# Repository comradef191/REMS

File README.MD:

# The RepRap Expansion Module System
A simple, open-source expansion system allowing easy addition of SPI, I2C, and GPIO devices to a controllerboard.

See [STANDARD.MD](Standard/STANDARD.MD) for details on module and slot design.
The KiCad footprint and symbol can be found in the [`/Footprint-Symbol`](/Footprint-Symbol) directory.

# Modules:

| Creator | Name           | Comment / Description                                          | Path                                      | Last Changed    |
|---------|----------------|----------------------------------------------------------------|-------------------------------------------|-----------------|
| Pera    | TLA2518 Module | Single-Sided SMD; Uses a TLA2518 to add 8 ADC inputs, over SPI. Untested. | [`Modules/TLA2518-8xThermistor`](Modules/TLA2518-8xThermistor) | March 22nd, 2024|

# License
Unless otherwise indicated, the contents of the [`/Modules`](/Modules) directory are licensed under CERN-OHL-v2+, see [LICENSE.txt](LICENSE.txt) for more details.

The contents of the [`/Standard`](/Standard) directory are licensed under CC0, see [CC0.txt](CC0.txt) for more details.

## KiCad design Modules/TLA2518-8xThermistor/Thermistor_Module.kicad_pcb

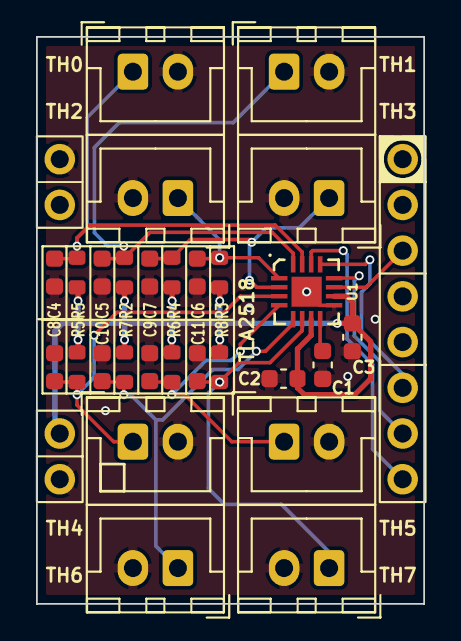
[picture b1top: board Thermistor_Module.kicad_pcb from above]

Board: 2 copper layers, 21.5 x 31.5 mm, 29 parts (0 on the bottom side), 15 nets.

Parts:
C1, C2, C3: 1uF; C_0603_1608Metric
C4, C5, C6, C7, C8, C9, C10, C11: 10uF; C_0603_1608Metric-DeSilked
J1, J2, J3, J4, J5, J6, J7, J8: Conn_01x02; JST_XH_B2B-XH-A_1x02_P2.50mm_Vertical
R1, R2, R3, R4, R5, R6, R7, R8: 4.7K; R_0603_1608Metric_De-Silked
U1: TLA2518
U2: REMS Stick

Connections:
+3V3: C2.1, C3.1, R1.1, R2.1, R3.1, R4.1, R5.1, R6.1, R7.1, R8.1, U1.7 (AVDD), U1.10 (DVDD), U2.15 (3V3)
/GPIO3: U1.11 (SPI_CS), U2.3 (IO3)
/SPI_SCK: U1.13 (SPI_SCK), U2.6 (SCK)
/SPI_SDI: U1.14 (SPI_SDI), U2.8 (SDI)
/SPI_SDO: U1.12 (SPI_SDO), U2.7 (SDO)
/THERMISTOR-0: C4.1, J1.1, R1.2, U1.15 (AIN0)
/THERMISTOR-1: C5.1, J2.1, R2.2, U1.16 (AIN1)
/THERMISTOR-2: C6.1, J3.1, R3.2, U1.1 (AIN2)
/THERMISTOR-3: C7.1, J4.1, R4.2, U1.2 (AIN3)
/THERMISTOR-4: C8.1, J5.1, R5.2, U1.3 (AIN4)
/THERMISTOR-5: C9.1, J6.1, R6.2, U1.4 (AIN5)
/THERMISTOR-6: C10.1, J7.1, R7.2, U1.5 (AIN6)
/THERMISTOR-7: C11.1, J8.1, R8.2, U1.6 (AIN7)
GND: C1.2, C2.2, C3.2, C4.2, C5.2, C6.2, C7.2, C8.2, C9.2, C10.2, C11.2, J1.2, J2.2, J3.2, J4.2, J5.2, J6.2, J7.2, J8.2, U1.9 (GND), U1.17 (GND), U2.9 (GND), U2.16 (GND)
unnamed: C1.1, U1.8 (DECAP)

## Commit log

2024-03-21 License
2024-03-22 Add TLA2518 ADC Module (UNTESTED)
2024-03-24 Add details on the standard, licensed under CC0, and flesh-out the ReadMe more.
2024-03-24 TLA2518: Mark pin 1
